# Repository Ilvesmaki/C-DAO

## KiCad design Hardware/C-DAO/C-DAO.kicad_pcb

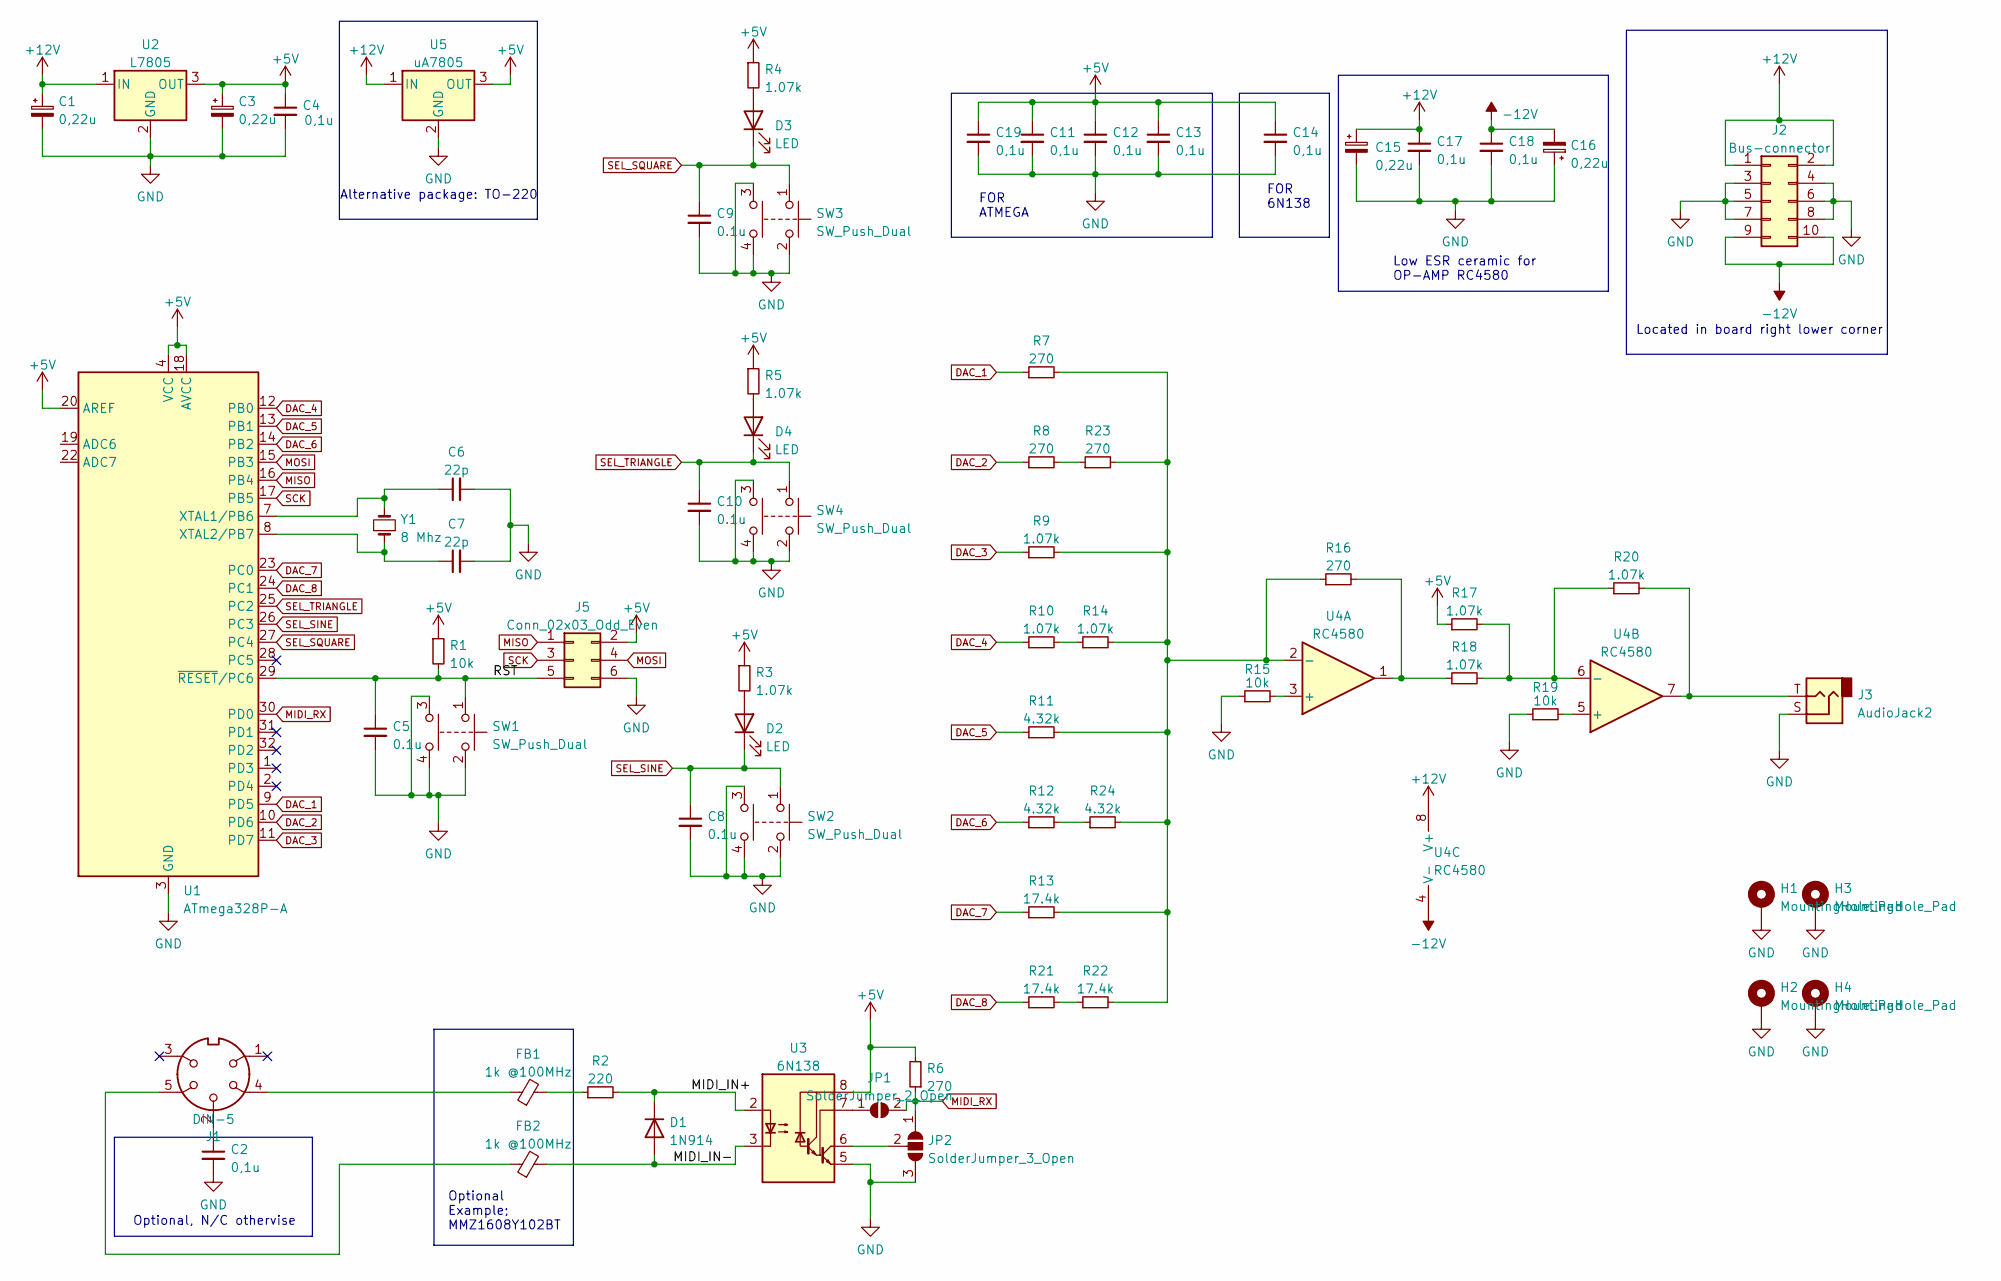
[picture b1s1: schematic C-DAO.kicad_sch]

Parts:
C1, C3, C15, C16: 0,22u; CP_Elec_4x5.4
C2, C4, C11, C12, C13, C14, C17, C18, C19: 0,1u; C_0603_1608Metric_Pad1.08x0.95mm_HandSolder
C5, C8, C9, C10: 0.1u; C_0603_1608Metric_Pad1.08x0.95mm_HandSolder
C6, C7: 22p; C_0603_1608Metric_Pad1.08x0.95mm_HandSolder
D1: 1N914; D_DO-35_SOD27_P7.62mm_Horizontal
D2, D3, D4: LED; LED_D5.0mm_Horizontal_O6.35mm_Z15.0mm
FB1, FB2: 1k @100MHz; L_0603_1608Metric_Pad1.05x0.95mm_HandSolder
H1, H2, H3, H4: MountingHole_Pad; MountingHole_3.2mm_M3_DIN965_Pad_TopBottom
J1: DIN-5; 5-pin DIN socket vertical
J2: Bus-connector; PinHeader_2x05_P2.54mm_Vertical
J3: AudioJack2; Cliff CL13843G 3.5mm mono jack
J5: Conn_02x03_Odd_Even; PinHeader_2x03_P2.54mm_Horizontal
JP1: SolderJumper_2_Open; SolderJumper-2_P1.3mm_Open_Pad1.0x1.5mm
JP2: SolderJumper_3_Open; SolderJumper-3_P1.3mm_Open_Pad1.0x1.5mm_NumberLabels
R1, R15, R19: 10k; R_0603_1608Metric_Pad0.98x0.95mm_HandSolder
R2: 220; R_0603_1608Metric_Pad0.98x0.95mm_HandSolder
R3, R4, R5, R9, R10, R14, R17, R18, R20: 1.07k; R_0603_1608Metric_Pad0.98x0.95mm_HandSolder
R6, R7, R8, R16, R23: 270; R_0603_1608Metric_Pad0.98x0.95mm_HandSolder
R11, R12, R24: 4.32k; R_0603_1608Metric_Pad0.98x0.95mm_HandSolder
R13, R21, R22: 17.4k; R_0603_1608Metric_Pad0.98x0.95mm_HandSolder
SW1, SW2, SW3, SW4: SW_Push_Dual; 1825968-2
U1: ATmega328P-A; TQFP-32_7x7mm_P0.8mm
U2: L7805; SOT-223-3_TabPin2
U3: 6N138; DIP-8_W7.62mm_LongPads
U4: RC4580; SOIC-8_3.9x4.9mm_P1.27mm
U5: uA7805; TO-220-3_Vertical
Y1: 8 Mhz; Crystal_SMD_HC49-SD

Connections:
+5V: C3.1, C4.1, C11.1, C12.1, C13.1, C14.1, C19.1, J5.2, R1.1, R3.1, R4.1, R5.1, R6.2, R17.1, U1.4 (VCC), U1.6 (VCC), U1.18 (AVCC), U1.20 (AREF), U2.3 (OUT), U3.8 (VCC), U5.3 (OUT)
+12V: C1.1, C15.1, C17.1, J2.1, J2.2, U2.1 (IN), U4.8 (V+), U5.1 (IN)
-12V: C16.2, C18.1, J2.9, J2.10, U4.4 (V-)
/MIDI_IN+: D1.1 (K), R2.2, U3.2 (C1)
/MIDI_IN-: D1.2 (A), FB2.2, U3.3 (C2)
/RST: C5.1, J5.5, R1.2, SW1.1, U1.29 (~RESET/PC6)
DAC_1: R7.1, U1.9 (PD5)
DAC_2: R8.1, U1.10 (PD6)
DAC_3: R9.1, U1.11 (PD7)
DAC_4: R10.1, U1.12 (PB0)
DAC_5: R11.1, U1.13 (PB1)
DAC_6: R12.1, U1.14 (PB2)
DAC_7: R13.1, U1.23 (PC0)
DAC_8: R21.1, U1.24 (PC1)
GND: C1.2, C2.2, C3.2, C4.2, C5.2, C6.2, C7.2, C8.2, C9.2, C10.2, C11.2, C12.2, C13.2, C14.2, C15.2, C16.1, C17.2, C18.2, C19.2, H1.1, H2.1, H3.1, H4.1, J2.3, J2.4, J2.5, J2.6, J2.7, J2.8, J3.S, J5.6, JP2.3 (B), R15.1, R19.1, SW1.2, SW1.3, SW1.4, SW2.2, SW2.3, SW2.4, SW3.2, SW3.3, SW3.4, SW4.2, SW4.3, SW4.4, U1.3 (GND), U1.5 (GND), U1.21 (GND), U2.2 (GND), U3.5 (GND), U5.2 (GND)
MIDI_RX: JP1.2 (B), JP2.1 (A), R6.1, U1.30 (PD0)
MISO: J5.1, U1.16 (PB4)
MOSI: J5.4, U1.15 (PB3)
unnamed: C2.1, J1.2
unnamed: C6.1, U1.7 (XTAL1/PB6), Y1.2
unnamed: C7.1, U1.8 (XTAL2/PB7), Y1.1
unnamed: D2.2 (A), R3.2
unnamed: D3.2 (A), R4.2
unnamed: D4.2 (A), R5.2
unnamed: FB1.1, J1.4
unnamed: FB1.2, R2.1
unnamed: FB2.1, J1.5
unnamed: J3.T, R20.2, U4.7
unnamed: JP1.1 (A), U3.7 (VO1)
unnamed: JP2.2 (C), U3.6 (VO2)
unnamed: R10.2, R14.1
unnamed: R7.2, R9.2, R11.2, R13.2, R14.2, R16.1, R22.2, R23.2, R24.2, U4.2 (-)
unnamed: R12.2, R24.1
unnamed: R15.2, U4.3 (+)
unnamed: R16.2, R18.1, U4.1
unnamed: R17.2, R18.2, R20.1, U4.6 (-)
unnamed: R19.2, U4.5 (+)
unnamed: R21.2, R22.1
unnamed: R8.2, R23.1
SCK: J5.3, U1.17 (PB5)
SEL_SINE: C8.1, D2.1 (K), SW2.1, U1.26 (PC3)
SEL_SQUARE: C9.1, D3.1 (K), SW3.1, U1.27 (PC4)
SEL_TRIANGLE: C10.1, D4.1 (K), SW4.1, U1.25 (PC2)

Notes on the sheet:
FOR ATMEGA
Optional, N/C othervise
Located in board right lower corner
Optional Example; MMZ1608Y102BT
Low ESR ceramic for OP-AMP RC4580
FOR 6N138
Alternative package: TO-220

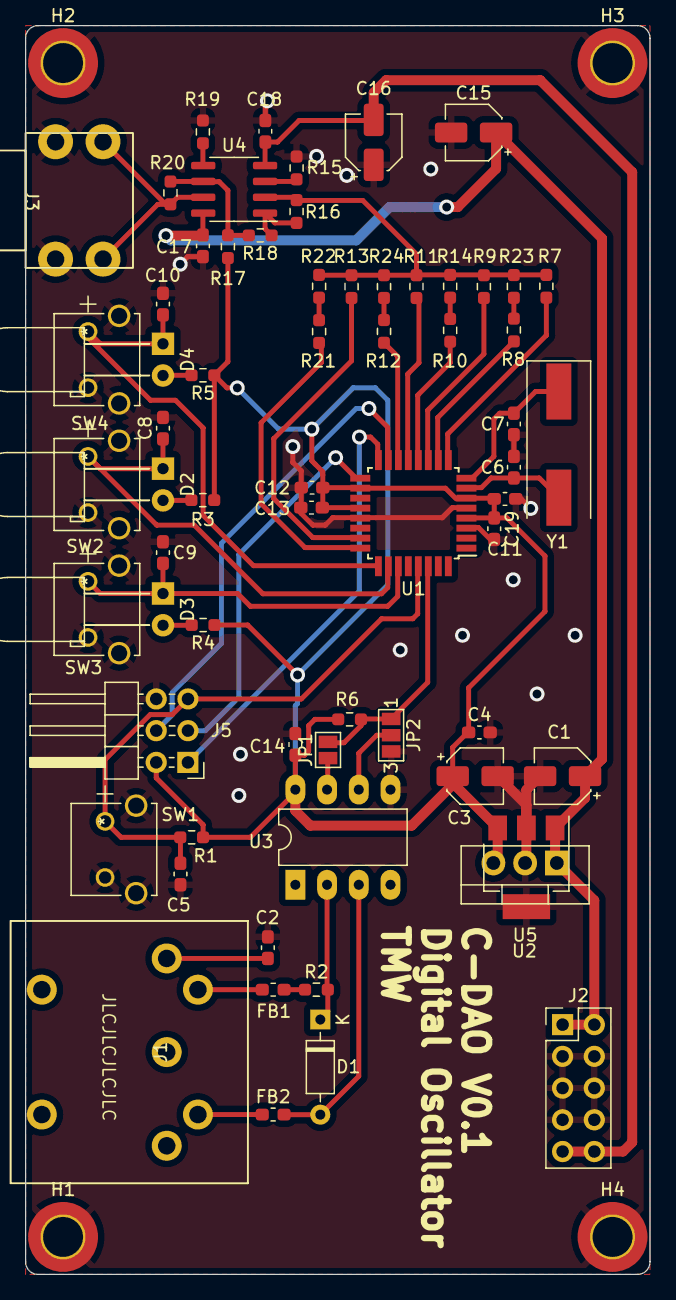
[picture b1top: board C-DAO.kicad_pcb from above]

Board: 2 copper layers, 50.0 x 100.0 mm, 69 parts (0 on the bottom side), 43 nets.

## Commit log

2022-02-28 Schematics and PCB V0.1 done
2022-03-15 Add production files and latest pcb files with bom
2022-03-21 Update 3d models and create wrl-model from board
2022-04-07 Add firmware project
2022-04-07 Add signal_generator and waveforms
2022-04-07 Add frequency module
2022-04-07 Add simple midi interface
2022-04-08 Add some much needed include guards
2022-04-08 Add midi notes
2022-04-08 Rename frequency module to timer

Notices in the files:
parts and their libraries:
Copyright 2021 Accelerated Designs. All rights reserved.
